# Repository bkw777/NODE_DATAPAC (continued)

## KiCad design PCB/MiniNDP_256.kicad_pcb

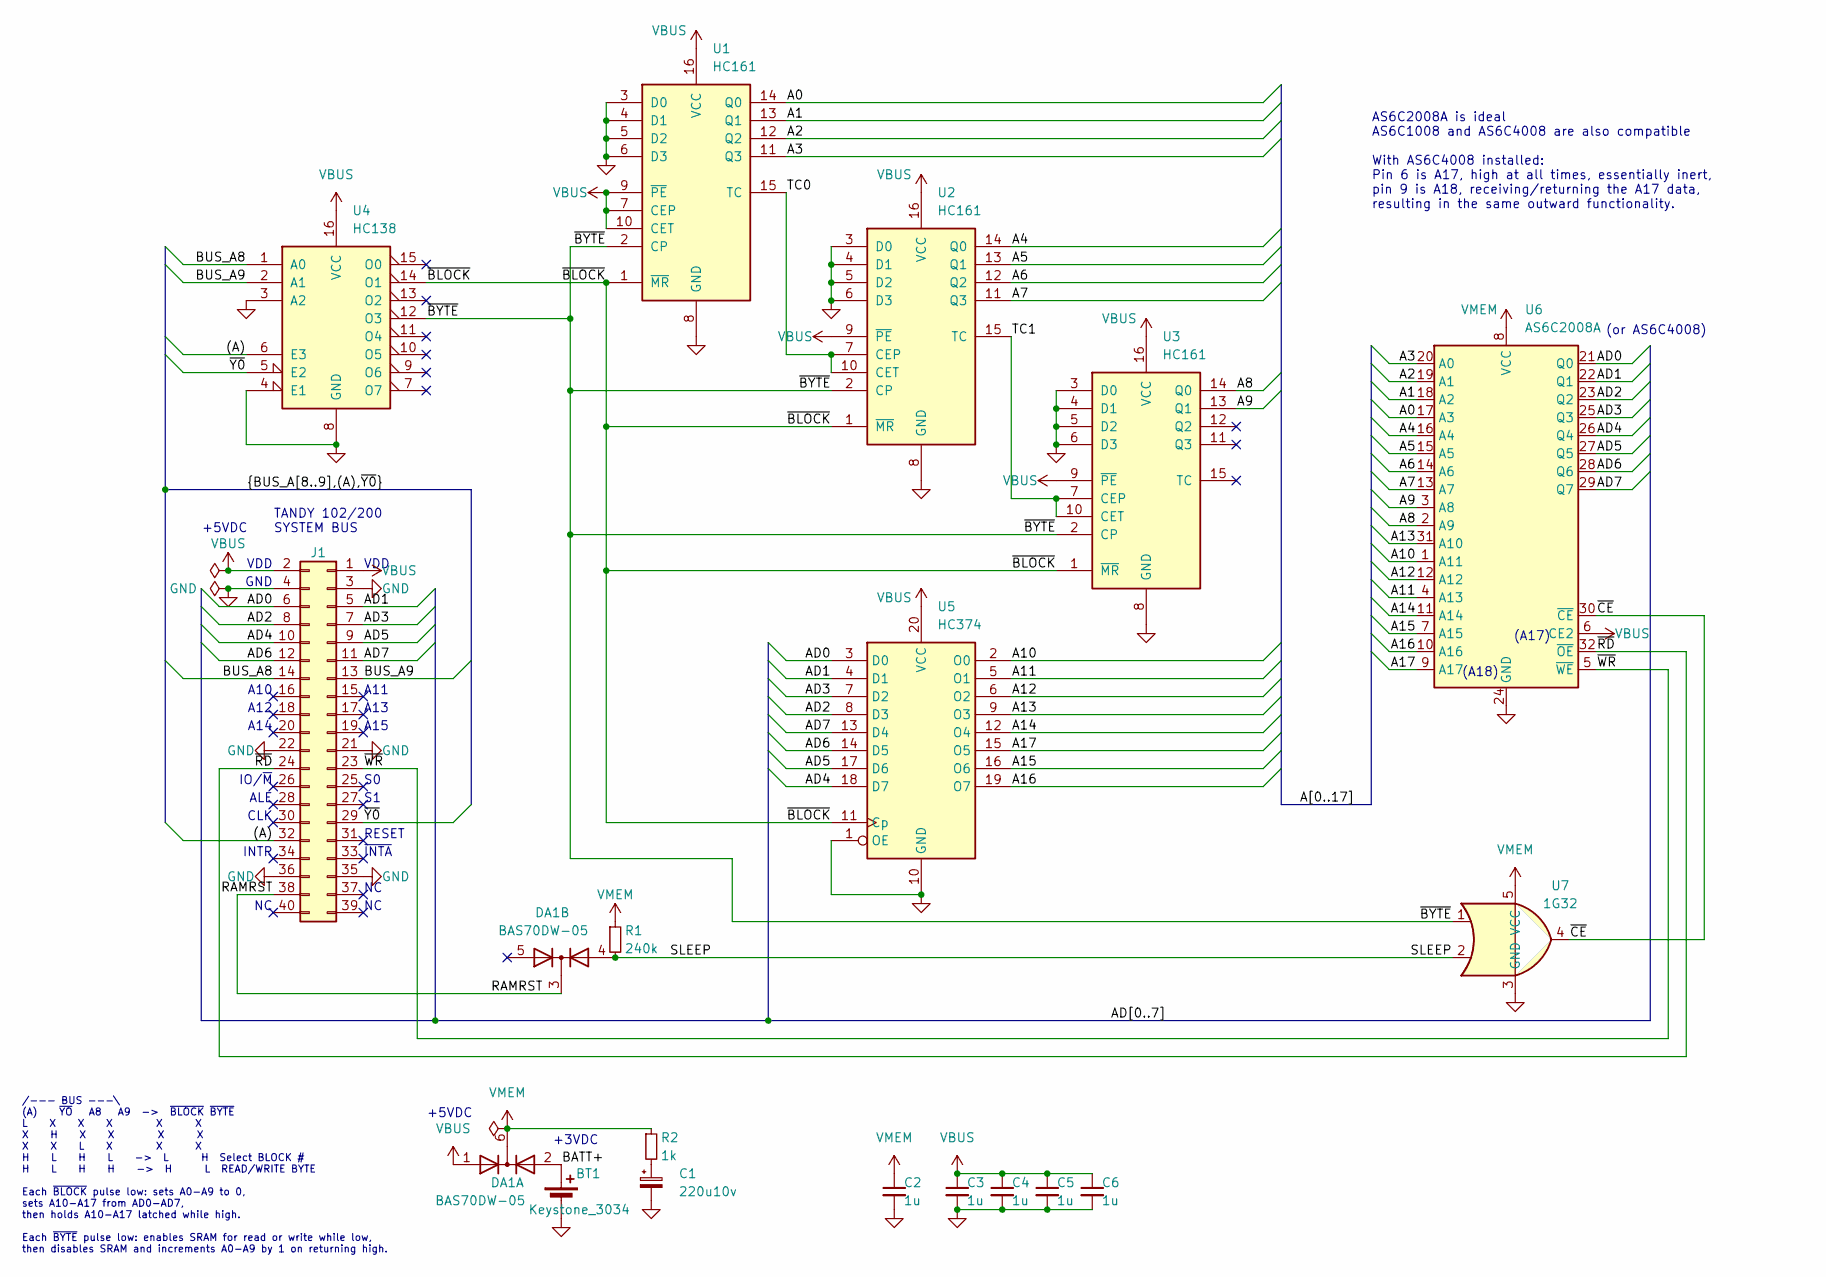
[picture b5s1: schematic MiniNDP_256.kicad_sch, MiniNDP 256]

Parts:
BT1: Keystone_3034; Keystone_3028_3034
C1: 220u10v; CP_6032
C2, C3, C4, C5, C6: 1u; C_0805
DA1: BAS70DW-05; SOT-363_SC-70-6_symmetric
J1: Conn_02x20_Odd_Even; IDC-Header_2x20_P2.54mm_Vertical
R1: 240k; R_0805
R2: 1k; R_0805
U1, U2, U3: HC161; TSSOP-16
U4: HC138; TSSOP-16
U5: HC374; TSSOP-20
U6: AS6C2008A; TSOP32-dual
U7: 1G32

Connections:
/(A): J1.32, U4.6 (E3)
/A0: U1.14 (Q0), U6.17 (A3)
/A1: U1.13 (Q1), U6.18 (A2)
/A2: U1.12 (Q2), U6.19 (A1)
/A3: U1.11 (Q3), U6.20 (A0)
/A4: U2.14 (Q0), U6.16 (A4)
/A5: U2.13 (Q1), U6.15 (A5)
/A6: U2.12 (Q2), U6.14 (A6)
/A7: U2.11 (Q3), U6.13 (A7)
/A8: U3.14 (Q0), U6.2 (A9)
/A9: U3.13 (Q1), U6.3 (A8)
/A10: U5.2 (O0), U6.1 (A11)
/A11: U5.5 (O1), U6.4 (A13)
/A12: U5.6 (O2), U6.12 (A12)
/A13: U5.9 (O3), U6.31 (A10)
/A14: U5.12 (O4), U6.11 (A14)
/A15: U5.16 (O6), U6.7 (A15)
/A16: U5.19 (O7), U6.10 (A16)
/A17: U5.15 (O5), U6.9 (A17)
/AD0: J1.6, U5.3 (D0), U6.21 (Q0)
/AD1: J1.5, U5.4 (D1), U6.22 (Q1)
/AD2: J1.8, U5.8 (D3), U6.23 (Q2)
/AD3: J1.7, U5.7 (D2), U6.25 (Q3)
/AD4: J1.10, U5.18 (D7), U6.26 (Q4)
/AD5: J1.9, U5.17 (D6), U6.27 (Q5)
/AD6: J1.12, U5.14 (D5), U6.28 (Q6)
/AD7: J1.11, U5.13 (D4), U6.29 (Q7)
/BATT+: BT1.1 (+), DA1.2 (A)
/BUS_A8: J1.14, U4.1 (A0)
/BUS_A9: J1.13, U4.2 (A1)
/CARRY0: U1.15 (TC), U2.7 (CEP), U2.10 (CET)
/CARRY1: U2.15 (TC), U3.7 (CEP), U3.10 (CET)
/RAMRST: DA1.3 (K), J1.38
/SLEEP: DA1.4 (A), R1.2, U7.2
/~BLOCK: U1.1 (~MR), U2.1 (~MR), U3.1 (~MR), U4.14 (O1), U5.11 (Cp)
/~BYTE: U1.2 (CP), U2.2 (CP), U3.2 (CP), U4.12 (O3), U7.1
/~CE: U6.30 (~CE), U7.4
/~RD: J1.24, U6.32 (~OE)
/~WR: J1.23, U6.5 (~WE)
/~Y0: J1.29, U4.5 (E2)
GND: BT1.2 (-), C1.2, C2.2, C3.2, C4.2, C5.2, C6.2, J1.3, J1.4, J1.21, J1.22, J1.35, J1.36, U1.3 (D0), U1.4 (D1), U1.5 (D2), U1.6 (D3), U1.8 (GND), U2.3 (D0), U2.4 (D1), U2.5 (D2), U2.6 (D3), U2.8 (GND), U3.3 (D0), U3.4 (D1), U3.5 (D2), U3.6 (D3), U3.8 (GND), U4.3 (A2), U4.4 (E1), U4.8 (GND), U5.1 (OE), U5.10 (GND), U6.24 (GND), U7.3 (GND)
unnamed: C1.1, R2.2
VBUS: C3.1, C4.1, C5.1, C6.1, DA1.1 (A), J1.1, J1.2, U1.7 (CEP), U1.9 (~PE), U1.10 (CET), U1.16 (VCC), U2.9 (~PE), U2.16 (VCC), U3.9 (~PE), U3.16 (VCC), U4.16 (VCC), U5.20 (VCC), U6.6 (CE2)
VMEM: C2.1, DA1.6 (K), R1.1, R2.1, U6.8 (VCC), U7.5 (VCC)

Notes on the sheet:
(A18)
TANDY 102/200 SYSTEM BUS
+5VDC
A15
INTR
A14
ALE
AS6C2008A is ideal AS6C1008 and AS6C4008 are also compatible With AS6C4008 installed: Pin 6 is A17, high at all times, essentially inert, pin 9 is A18, receiving/returning the A17 data, resulting in the same outward functionality.
~{INTA}
CLK
GND
IO/~{M}
VDD
A10
(A17)
/--- BUS ---\ (A) ~{YO} A8 A9 -> ~{BLOCK} ~{BYTE} L X X X X X X H X X X X X X L X X X H L H L -> L H Select BLOCK # H L H H -> H L READ/WRITE BYTE Each ~{BLOCK} pulse low: sets A0-A9 to 0, sets A10-A17 from AD0-AD7, then holds A10-A17 latched while high. Each ~{BYTE} pulse low: enables SRAM for rea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
+3VDC
RESET
A11
A13
(or AS6C4008)
A12

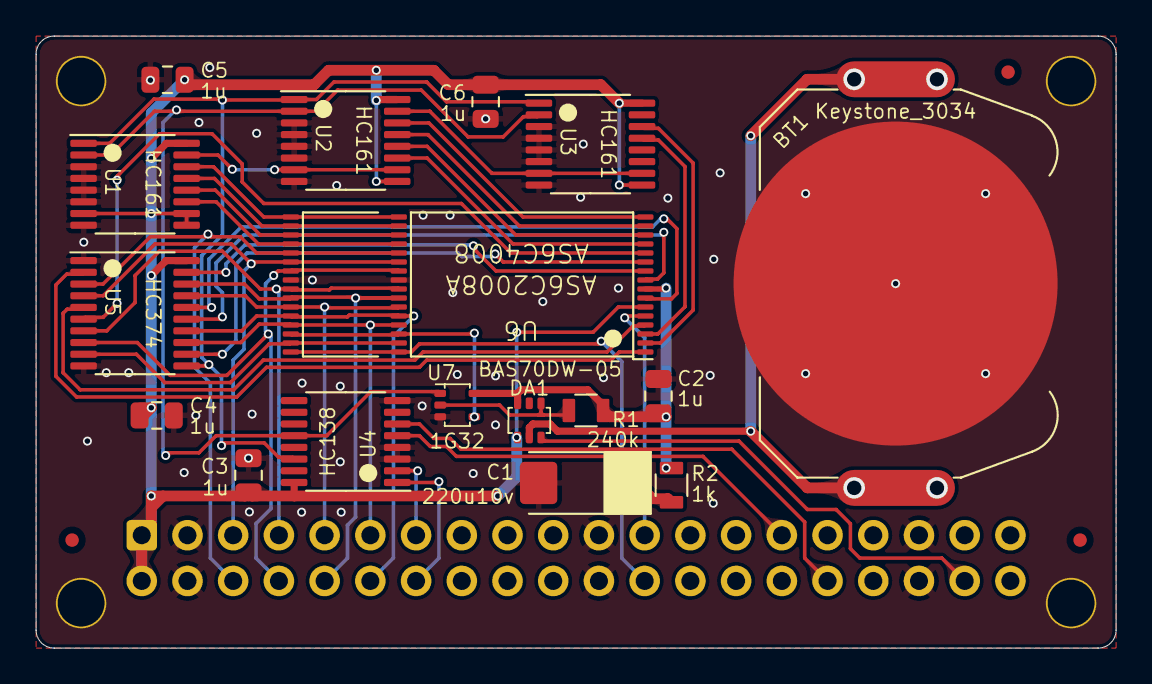
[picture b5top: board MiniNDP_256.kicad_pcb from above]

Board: 2 copper layers, 60.0 x 34.0 mm, 25 parts (1 on the bottom side), 44 nets.

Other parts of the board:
F1, F2, F3: Fiducial_0.75_1.5
M1, M2, M3, M4: MountHole_M2.5

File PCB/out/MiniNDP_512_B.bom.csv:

"Reference","Value","Datasheet","Footprint","Qty","DNP","MPN","Description"
"BT1","Keystone_3034","datasheets/Keystone_3034.pdf","000_LOCAL:Keystone_3028_3034","1","","Keystone 3034","SMT 20mm x 3.2mm coin cell holder"
"C1","220u10v","datasheets/TAJ.odf","000_LOCAL:CP_6032","1","","TAJC227K010RNJ","CAP TANT 220UF 10% 10V 2312"
"C2,C3,C4,C5","1u","datasheets/CL21B105KAFNNNE.pdf","000_LOCAL:C_0805","4","","CL21B105KAFNNNE","CAP CER 1UF 25V X7R 0805"
"DA1","BAS70DW-05","datasheets/BAS70.pdf","000_LOCAL:SOT-363_SC-70-6_symmetric","1","","BAS70DW-05-7-F","DIODE ARR SCHOTT 70V 70MA SOT363 2-PAIR COMMON-CATHODE"
"J1","Conn_02x20_Odd_Even","datasheets/2x20_male_boxed.pdf","000_LOCAL:IDC-Header_2x20_P2.54mm_Vertical","1","","302-S401","CONN HEADER VERT 40POS 2.54MM"
"R1","1k","datasheets/RK73.pdf","000_LOCAL:R_0805","1","","RK73B2ATTD102J","RES 1K OHM 5% 1/4W 0805"
"R2","47k","datasheets/sei-rmcf_rmcp.pdf","000_LOCAL:R_0805","1","","RMCF0805FT47K0","RES 47K OHM 1% 1/8W 0805"
"U1,U2,U3","HC161","datasheets/HC161.pdf","000_LOCAL:TSSOP-16","3","","74HC161PW,118","IC BINARY COUNTER 4-BIT 16TSSOP"
"U4","HC138","datasheets/HC138.pdf","000_LOCAL:TSSOP-16","1","","74HC138PW,118","IC DECODER/DEMUX 1X3:8 16TSSOP"
"U5","FCT821","datasheets/CY74FCT821T.pdf","000_LOCAL:SOIC-24","1","","CY74FCT821BTSOC","IC FF D-TYPE SNGL 10BIT 24SOIC"
"U6","AS6C4008","datasheets/AS6C4008.pdf","000_LOCAL:TSOP-II-SOP-32_dual","1","","AS6C4008-55ZIN","IC SRAM 512Kx8 PARALLEL 5v TSOP-II-32"
"U7","1G32","datasheets/LVC1G32.pdf","000_LOCAL:SOT-353_SC-70-5","1","","74LVC1G32GW,125","IC GATE OR 1CH 2-INP 5TSSOP"

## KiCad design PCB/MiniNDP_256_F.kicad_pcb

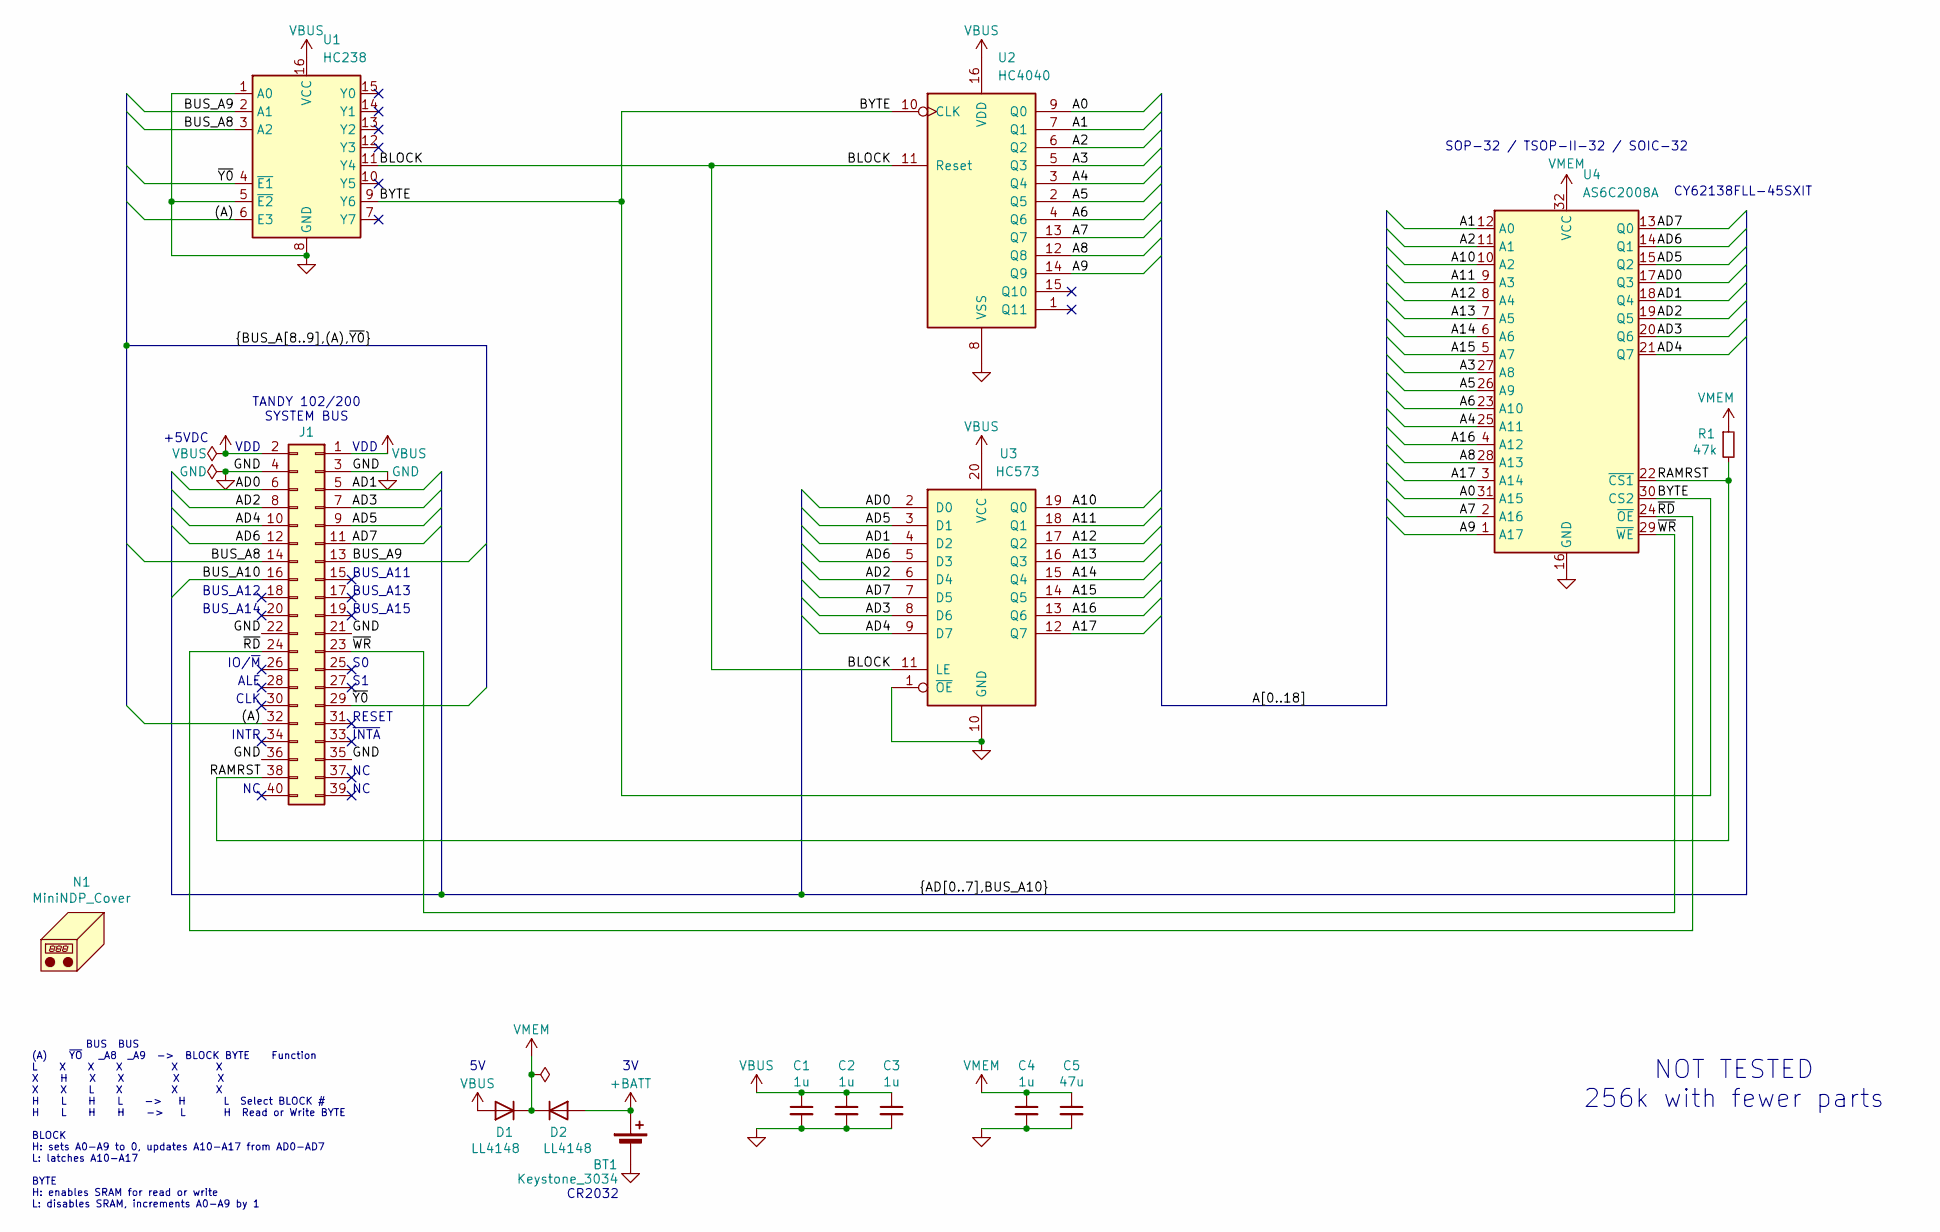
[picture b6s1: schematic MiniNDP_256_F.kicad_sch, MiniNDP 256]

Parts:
BT1: Keystone_3034; Keystone_3028_3034; MPN Keystone 3034
C1, C2, C3, C4: 1u; C_1206; MPN CL31B105KAHNNNE
C5: 47u; C_1206; MPN C3216X5R1E476M160DC
D1, D2: LL4148; D_MiniMELF; MPN FDLL4148
J1: Conn_02x20_Odd_Even; IDC-Header_2x20_P2.54mm_Vertical; MPN 302-S401
N1: MiniNDP_Cover; MPN MiniNDP_Cover.stl
R1: 47k; R_1206; MPN CRGCQ1206F47K
U1: HC238; SOIC-16_3.9x9.9mm_P1.27mm; MPN 74HC238D,653
U2: HC4040; SOIC-16_3.9x9.9mm_P1.27mm; MPN 74HC4040D,653
U3: HC573; SOIC-20W_7.5x12.8mm_P1.27mm; MPN 74HC573D,653
U4: AS6C2008A; TSOP-II-SOP-32_dual; MPN AS6C2008A-55SIN

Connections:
+BATT: BT1.1 (+), D2.2 (A)
/(A): J1.32, U1.6 (E3)
/A0: U2.9 (Q0), U4.31 (A15)
/A1: U2.7 (Q1), U4.12 (A0)
/A2: U2.6 (Q2), U4.11 (A1)
/A3: U2.5 (Q3), U4.27 (A8)
/A4: U2.3 (Q4), U4.25 (A11)
/A5: U2.2 (Q5), U4.26 (A9)
/A6: U2.4 (Q6), U4.23 (A10)
/A7: U2.13 (Q7), U4.2 (A16)
/A8: U2.12 (Q8), U4.28 (A13)
/A9: U2.14 (Q9), U4.1 (A17)
/A10: U3.19 (Q0), U4.10 (A2)
/A11: U3.18 (Q1), U4.9 (A3)
/A12: U3.17 (Q2), U4.8 (A4)
/A13: U3.16 (Q3), U4.7 (A5)
/A14: U3.15 (Q4), U4.6 (A6)
/A15: U3.14 (Q5), U4.5 (A7)
/A16: U3.13 (Q6), U4.4 (A12)
/A17: U3.12 (Q7), U4.3 (A14)
/AD0: J1.6, U3.2 (D0), U4.17 (Q3)
/AD1: J1.5, U3.4 (D2), U4.18 (Q4)
/AD2: J1.8, U3.6 (D4), U4.19 (Q5)
/AD3: J1.7, U3.8 (D6), U4.20 (Q6)
/AD4: J1.10, U3.9 (D7), U4.21 (Q7)
/AD5: J1.9, U3.3 (D1), U4.15 (Q2)
/AD6: J1.12, U3.5 (D3), U4.14 (Q1)
/AD7: J1.11, U3.7 (D5), U4.13 (Q0)
/BLOCK: U1.11 (Y4), U2.11 (Reset), U3.11 (LE)
/BUS_A8: J1.14, U1.3 (A2)
/BUS_A9: J1.13, U1.2 (A1)
/BUS_A10: J1.16
/BYTE: U1.9 (Y6), U2.10 (CLK), U4.30 (CS2)
/RAMRST: J1.38, R1.2, U4.22 (~CS1)
/~RD: J1.24, U4.24 (~OE)
/~WR: J1.23, U4.29 (~WE)
/~Y0: J1.29, U1.4 (~E1)
GND: BT1.2 (-), C1.2, C2.2, C3.2, C4.2, C5.2, J1.3, J1.4, J1.21, J1.22, J1.35, J1.36, U1.1 (A0), U1.5 (~E2), U1.8 (GND), U2.8 (VSS), U3.1 (~OE), U3.10 (GND), U4.16 (GND)
VBUS: C1.1, C2.1, C3.1, D1.2 (A), J1.1, J1.2, U1.16 (VCC), U2.16 (VDD), U3.20 (VCC)
VMEM: C4.1, C5.1, D1.1 (K), D2.1 (K), R1.1, U4.32 (VCC)

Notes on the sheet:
BUS_A11
TANDY 102/200 SYSTEM BUS
+5VDC
BUS_A15
CY62138FLL-45SXIT
INTR
BUS_A14
ALE
SOP-32 / TSOP-II-32 / SOIC-32
NOT TESTED 256k with fewer parts
~{INTA}
CR2032
CLK
IO/~{M}
VDD
RESET
BUS_A13
BUS BUS (A) ~{YO} _A8 _A9 -> BLOCK BYTE Function L X X X X X X H X X X X X X L X X X H L H L -> H L Select BLOCK # H L H H -> L H Read or Write BYTE BLOCK H: sets A0-A9 to 0, updates A10-A17 from AD0-AD7 L: latches A10-A17 BYTE H: enables SRAM for read or write L: disables SRAM, increments A0-A9 by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
BUS_A12

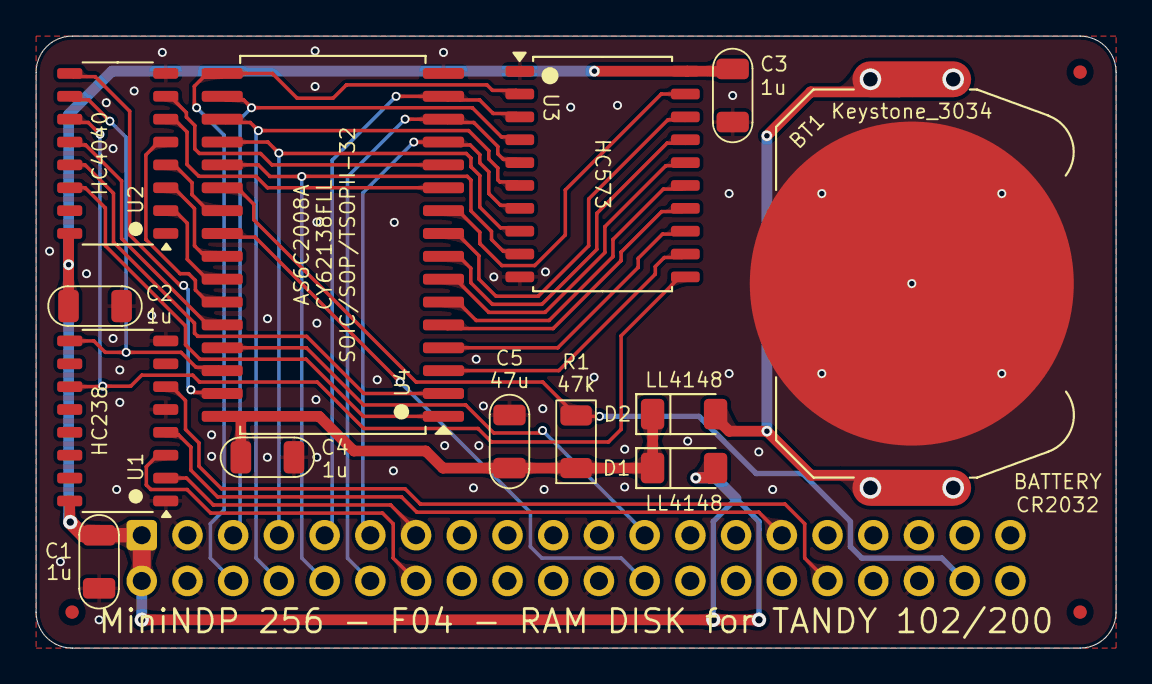
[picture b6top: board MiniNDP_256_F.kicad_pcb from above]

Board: 2 copper layers, 60.0 x 34.0 mm, 18 parts (1 on the bottom side), 39 nets.

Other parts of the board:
F2, F2#2, F3: Fiducial_0.75_1.5

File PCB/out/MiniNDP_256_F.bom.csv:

"Reference","Value","Datasheet","Footprint","Qty","DNP","MPN","Description"
"BT1","Keystone_3034","datasheets/Keystone_3034.pdf","000_LOCAL:Keystone_3028_3034","1","","Keystone 3034","SMT 20mm x 3.2mm coin cell holder"
"C1,C2,C3,C4","1u","datasheets/CL05Y105KP6VPN.pdf","000_LOCAL:C_1206","4","","CL31B105KAHNNNE","CAP CER 1UF 25V X7R 1206"
"C5","47u","datasheets/TDK_MLCC_Cxxxx.pdf","000_LOCAL:C_1206","1","","C3216X5R1E476M160DC","CAP CER 47UF 25V X5R 1206"
"D1,D2","LL4148","datasheets/ll4148.pdf","000_LOCAL:D_MiniMELF","2","","FDLL4148","50V 1A General Purpose Rectifier Diode"
"J1","Conn_02x20_Odd_Even","datasheets/2x20_male_boxed.pdf","000_LOCAL:IDC-Header_2x20_P2.54mm_Vertical","1","","302-S401","CONN HEADER VERT 40POS 2.54MM"
"R1","47k","datasheets/TE-4-2176343-5.pdf","000_LOCAL:R_1206","1","","CRGCQ1206F47K","RES 47K OHM 1% 1/4W 1206"
"U1","HC238","datasheets/HC238.pdf","000_LOCAL:SOIC-16_3.9x9.9mm_P1.27mm","1","","74HC238D,653","IC DECODER/DEMUX 1 X 3:8 16SO"
"U2","HC4040","datasheets/4040.pdf","000_LOCAL:SOIC-16_3.9x9.9mm_P1.27mm","1","","74HC4040D,653","IC BINARY COUNTER 12-BIT 16SO"
"U3","HC573","datasheets/HC573.pdf","000_LOCAL:SOIC-20W_7.5x12.8mm_P1.27mm","1","","74HC573D,653","IC D-TYPE TRANSP SGL 8:8 20SO"
"U4","AS6C2008A","datasheets/AS6C2008A.pdf","000_LOCAL:TSOP-II-SOP-32_dual","1","","AS6C2008A-55SIN","256K x 8 High-Speed CMOS Static RAM, 55/70ns, DIP-32/SOP-32"
